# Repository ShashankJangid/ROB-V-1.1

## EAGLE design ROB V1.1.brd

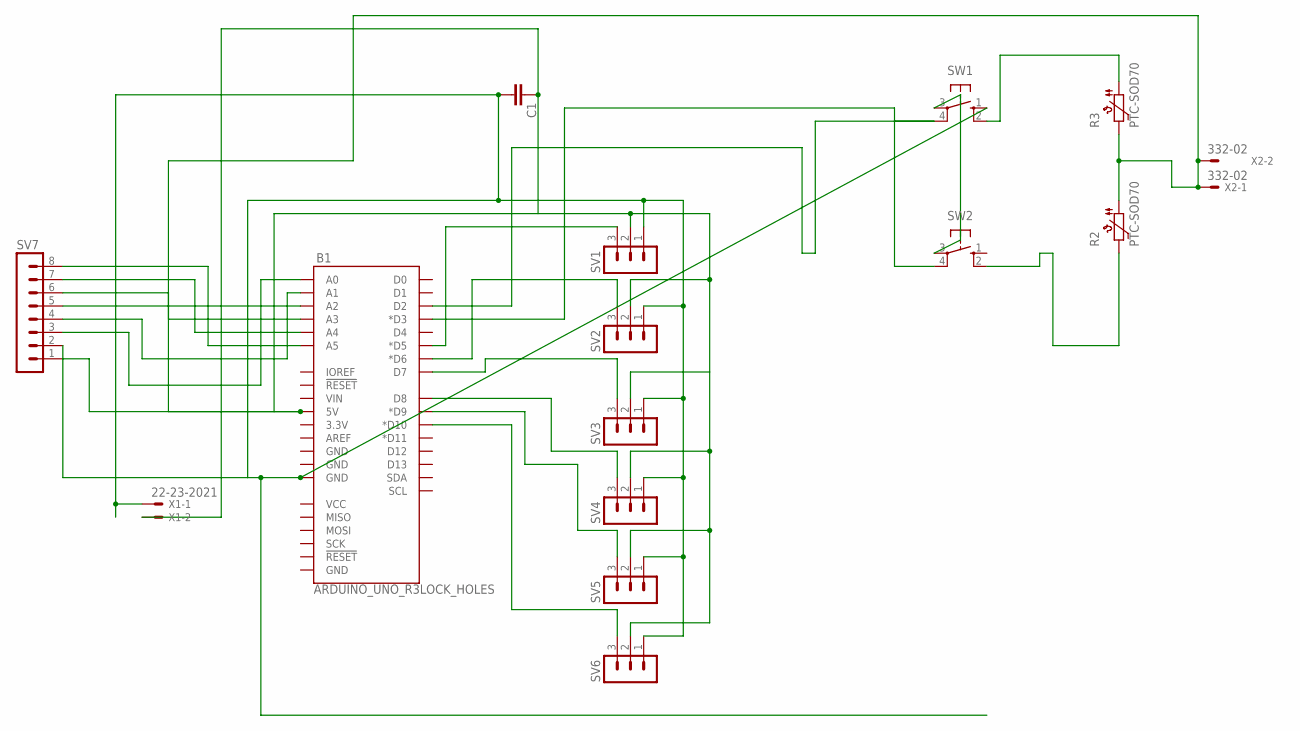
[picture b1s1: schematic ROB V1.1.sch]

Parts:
B1: ARDUINO_UNO_R3LOCK_HOLES; ARDUINO_R3_LOCK_HOLES
C1: C2.5/2; C2.5-2
R2, R3: PTC-SOD70; SOD70
SV1, SV2, SV3, SV4, SV5, SV6: MA03-1
SV7: MA08-1
SW1, SW2: 10-XX; B3F-10XX
X1: 22-23-2021
X2: 332-02

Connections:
5V: B1.5V, C1.1, R2.1, R3.2, SV1.2, SV2.2, SV3.2, SV4.2, SV5.2, SV6.2, SV7.1, X1.2, X2.1, X2.2
D2: B1.D2, SW1.4 (P1)
D3: B1.D3 (*D3), SW2.4 (P1)
D5: B1.D5 (*D5), SV1.3
D6: B1.D6 (*D6), SV2.3
D7: B1.D7, SV3.3
D8: B1.D8, SV4.3
D9: B1.D9 (*D9), SV5.3
D10: B1.D10 (*D10), SV6.3
GND: B1.GND@2 (GND), C1.2, SV1.1, SV2.1, SV3.1, SV4.1, SV5.1, SV6.1, SV7.2, SW1.1 (S), X1.1
unnamed: B1.A5, SV7.8
unnamed: B1.A4, SV7.7
unnamed: B1.A3, SV7.6
unnamed: B1.A2, SV7.5
unnamed: B1.A1, SV7.4
unnamed: R3.1, SW1.2 (S1)
unnamed: B1.A0, SV7.3
S-R: R2.2, SW2.2 (S1)
S-S: SW1.3, SW2.3

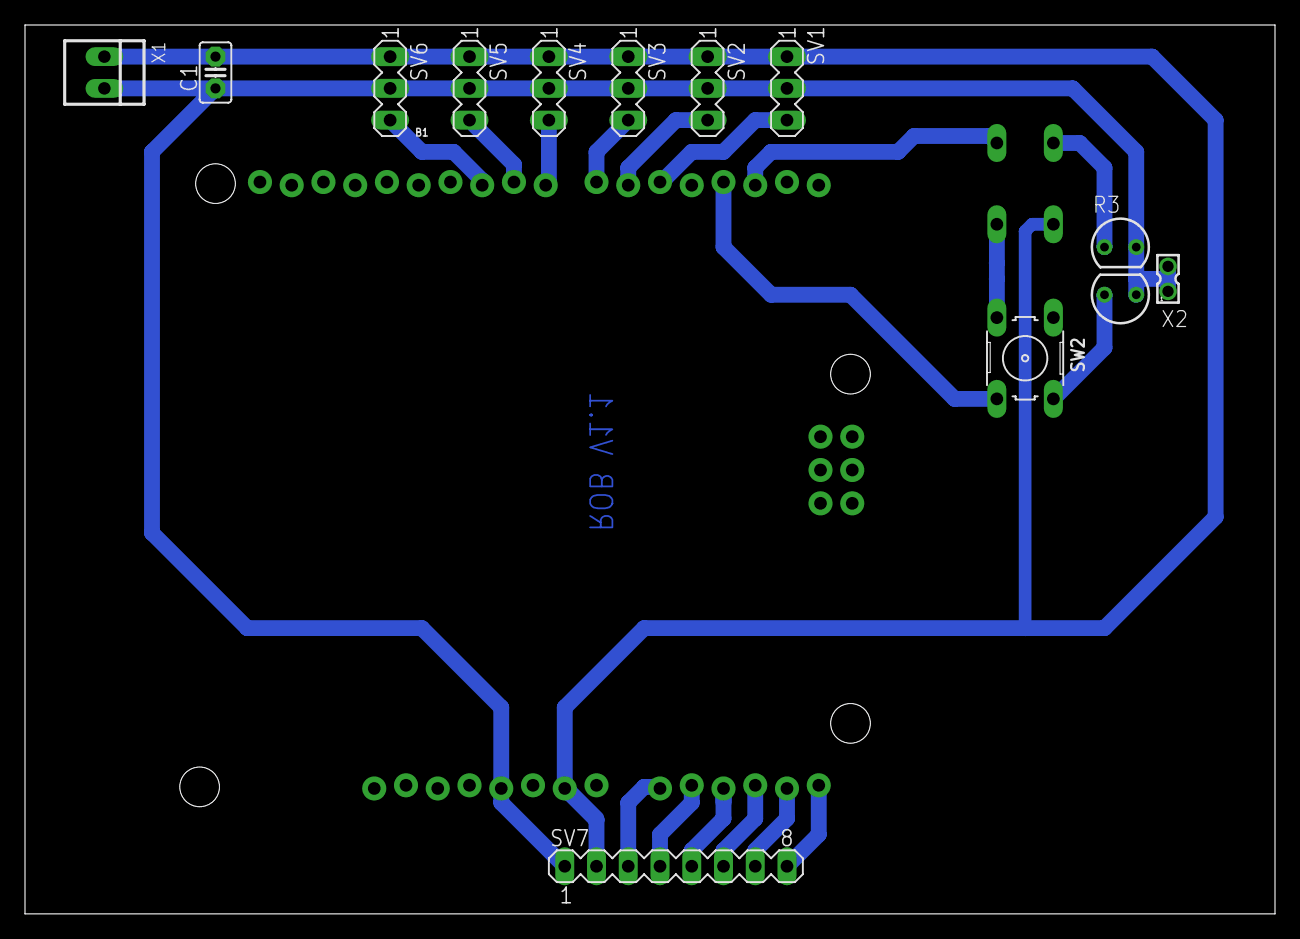
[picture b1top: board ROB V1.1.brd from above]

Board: 2 copper layers, 100.0 x 71.1 mm, 15 parts (1 on the bottom side), 19 nets.

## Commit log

2025-09-23 Add files via upload
    First Controlling Servo with the Potentiometer
2025-09-23 Create Using_Arrays_for_servo
    67-line code to just 17 lines by using arrays for servos, Potentiometer Pin and Delays
2025-09-23 Update Using_Arrays_for_servo
2025-09-24 Create ROB V1.1 With Record and Play Button
    Create ROB V1.1 With Record and Play Button
2025-09-26 Update ROB V1.1 With Record and Play Button
2025-09-28 Schematic and Board File for ROB V 1.1
    Schematic and Board File for ROB V 1.1

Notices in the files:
parts and their libraries:
Arduino Uno: Licensing: Creative Commons ShareAlike 4.0 International - https://creativecommons.org/licenses/by-sa/4.0
